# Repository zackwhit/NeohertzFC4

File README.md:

### About
NeohertzFC4 is my version of of a STM32F405 based flight controller, meant to operate quadcopters.
I developed this because I was curious what really went into the development of a flight controller; they seemed like relatively simple 
devices to cost so much. My goal was to develop something relatively simple and low-cost, and so that's why I opted to use the STM32F4 rather than an F7. Other 
open source designs (there aren't many!) aren't easy to interact with or order: they aren't in KiCAD and aren't on GitHub/Gitlab. So another one of my goals was to
provide a sort of template that would not only make my own development easier, but make it easier for other people as well. 

#### Features
- STM32F405RGTx main computing chip
- BMP280 barometer
- MMA8452QR1 accelerometer
- LIS3MDL magnometer
- AT7456 analog OSD chip
  
Bonus: LIS3DH accelerometer included as well, since I wanted to add support for it in betaflight. It doesn't have to be populated

### Updates
- July 19th, 2023: I ordered the parts for the first 5 prototypes after working on the design for about a week. All the parts should be here in about two weeks.

### Known Issues
- The JLCPCB information isn't exactly correct in REV001, I would not recomend ordering it at this stage unless you know what you're doing.

### Potential issues
- There aren't many (if any at all) alternative parts for certain ICs. If one were to go out of stock, a small redesign would have to be done to use a different solution.
- As of right now, the hardware is completely untested.

### How to build one!
- Order the PCBs through JLCPCB, I recomend only having them populate the passive components for you at this stage of the project.
- Order your components; I suggest through LCSC
- Assemble! This is a double sided PCB, but you can ignore the bottom side if you don't want to use the analog OSD chip included there.
- Profit.

### Future plans
As of the first revision, there is only one onboard BEC. This means there is only a 5V rail and no 9v (or 10v/12v) rails for a digital 
video system. I am planning on adding a second BEC for that purpose, but it didn't fit with my initial goal of having all the core components on
the top of the PCB. 

I'm also interested in creating a version of this with an AT32 chip instead of an STM32. As far as I can tell they are cheaper, but not necessarily more
available. I'm inclined to making a board that can have either an AT32 or an STM32 chip, that way you could just select whichever one is best at the time. 
Of course, this hinges on betaflight actually having decent support for AT32 chips, since I don't personally have time to add support. 

Other (optional) features I'm interested in adding:
- ELRS receiver built-in, both 900MHz and 2.4GHz options would be great so as to support long range flying.

#### License
GNU General Public License v3.0

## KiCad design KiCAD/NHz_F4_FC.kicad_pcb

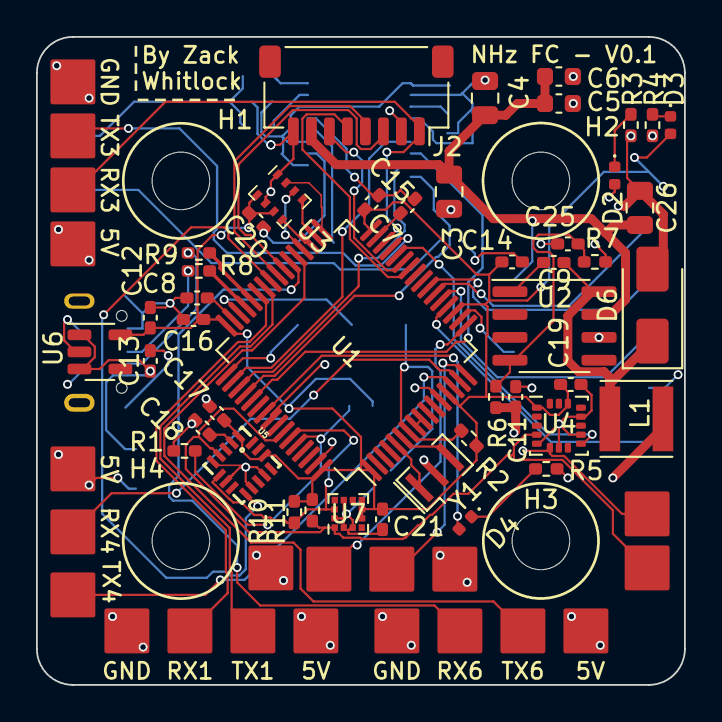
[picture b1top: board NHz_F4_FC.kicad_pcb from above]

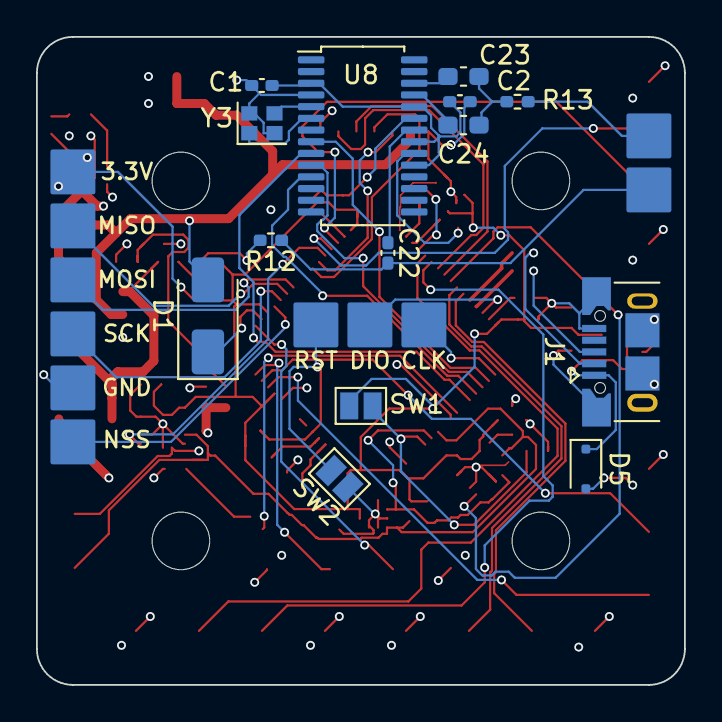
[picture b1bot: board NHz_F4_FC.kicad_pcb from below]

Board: 4 copper layers, 36.0 x 36.0 mm, 95 parts (25 on the bottom side), 66 nets.

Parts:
C1, C2, C9, C22: 100nF; C_0402_1005Metric_Pad0.74x0.62mm_HandSolder
C3, C4, C26: 4.7uF; C_0805_2012Metric
C5: 1uF; C_0603_1608Metric
C6: 0.1uF; C_0603_1608Metric
C7, C8: 2.2uF; C_0402_1005Metric_Pad0.74x0.62mm_HandSolder
C11, C12, C13, C14, C15, C16: 10uF; C_0402_1005Metric_Pad0.74x0.62mm_HandSolder
C17, C19, C20, C21: 4.7uF; C_0402_1005Metric_Pad0.74x0.62mm_HandSolder
C18: 0.1uF; C_0402_1005Metric_Pad0.74x0.62mm_HandSolder
C23, C24: 47uF; C_0603_1608Metric_Pad1.08x0.95mm_HandSolder
C25: 100p; C_0402_1005Metric_Pad0.74x0.62mm_HandSolder
D1: D_TVS; D_SMA
D2, D3, D4: LED; LED_0402_1005Metric
D5: D_Small; D_SOD-323F
D6: B340; D_SMA
H1, H2, H3, H4: MountingHole; MountingHole_3.2mm_M3
J1: USB_B_Micro; USB_Micro-B_XKB_U254-051T-4BH83-F1S
J2: Conn_01x08_Socket; JST_SH_SM08B-SRSS-TB_1x08-1MP_P1.00mm_Horizontal
L1: 22uH; L_Vishay_IFSC-1515AH_4x4x1.8mm
R1, R2, R6: 10k; R_0402_1005Metric_Pad0.72x0.64mm_HandSolder
R3, R4, R5: 1k; R_0402_1005Metric_Pad0.72x0.64mm_HandSolder
R7: 3.3k; R_0402_1005Metric_Pad0.72x0.64mm_HandSolder
R8, R9: 22; R_0402_1005Metric_Pad0.72x0.64mm_HandSolder
R10, R11: 2.2k; R_0402_1005Metric_Pad0.72x0.64mm_HandSolder
R12, R13: 75; R_0402_1005Metric_Pad0.72x0.64mm_HandSolder
SW1, SW2: SW_Push; SolderJumper-2_P1.3mm_Open_Pad1.0x1.5mm
TP1, TP2, TP3, TP4, TP5, TP6, TP7, TP8, TP9, TP10, TP11, TP12, TP13, TP14, TP15, TP16, TP17, TP18, TP19, TP20, TP21, TP22, TP23, TP24, TP25, TP26, TP27, TP28, TP29, TP30, TP31, TP32: TestPoint; SolderPad_2.5x2.5
U1: STM32F405RGTx; LQFP-64_10x10mm_P0.5mm
U2: TPS5420D; SOIC-8_3.9x4.9mm_P1.27mm
U3: BMP280; Bosch_LGA-8_2x2.5mm_P0.65mm_ClockwisePinNumbering
U4: LIS3DH; LGA-16_3x3mm_P0.5mm_LayoutBorder3x5y
U5: MMA8452QR1; QFN-16_0.5MM
U6: XC6219B332MR; SOT-23-5
U7: LIS3MDL; LGA-12_2x2mm_P0.5mm
U8: AT7456; TSSOP-28_4.4x9.7mm_P0.65mm
Y1: CSTCE8M00G52-R0; Resonator_SMD_Murata_CSTxExxV-3Pin_3.0x1.1mm
Y3: Crystal_GND24; Crystal_SMD_2016-4Pin_2.0x1.6mm

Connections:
+3.3V: C12.1, C14.1, C15.1, C16.1, C17.1, C19.1, C20.1, C21.1, D3.2 (A), R2.1, R10.2, R11.2, SW1.1, TP18.1, U1.1 (VBAT), U1.13 (VDDA), U1.19 (VDD), U1.32 (VDD), U1.48 (VDD), U1.64 (VDD), U3.6 (VDDIO), U3.8 (VDD), U4.1 (VDD_IO), U4.14 (VDD), U5.1 (VDDIO), U5.14 (VDD), U6.5 (VOUT), U7.5 (Vdd), U7.6 (Vdd_IO)
+5V: C11.1, C25.2, D2.2 (A), D5.2 (A), L1.2, R6.1, TP17.1, TP19.1, TP20.1, TP26.1, TP28.1
+BATT: C3.1, C4.1, C5.1, C6.1, C26.1, D1.2 (A2), J2.7, U2.7 (VIN)
/CUR: J2.2, U1.56 (PB4)
/LIS3DH_INT_PIN: U1.28 (PB2), U4.9 (INT2)
/M1: J2.6, U1.27 (PB1)
/M2: J2.5, U1.26 (PB0)
/M3: J2.4, U1.40 (PC9)
/M4: J2.3, U1.39 (PC8)
/MISO2: U1.35 (PB14), U3.5 (SDO)
/MISO3: U1.52 (PC11), U8.11 (SDOUT)
/MMA8451_INT_PIN: U1.41 (PA8), U5.9 (INT2)
/MOSI2: U1.36 (PB15), U3.3 (SDI)
/MOSI3: U1.53 (PC12), U8.9 (SDIN)
/RX3: J2.1, TP14.1, U1.30 (PB11)
/SCK2: U1.34 (PB13), U3.4 (SCK)
/SCK3: U1.51 (PC10), U8.10 (SCLK)
/SCL1: R11.1, TP11.1, U1.58 (PB6), U4.4 (SCL/SPC), U5.4 (SCL), U7.1 (SCL/SPC)
/SDA1: R10.1, TP12.1, U1.59 (PB7), U4.6 (SDA/SDI/SDO), U5.6 (SDA), U7.11 (SDA/SDI/SDO)
/SS2: U1.33 (PB12), U3.2 (CSB)
/SS3: U1.50 (PA15), U8.8 (CS)
/STM32F405RGTx/PA0_TX4: TP10.1, U1.14 (PA0)
/STM32F405RGTx/PA1_RX4: TP9.1, U1.15 (PA1)
/STM32F405RGTx/PA2_TX2: TP8.1, U1.16 (PA2)
/STM32F405RGTx/PA3_RX2: TP7.1, U1.17 (PA3)
/STM32F405RGTx/PA4_NSS1: TP6.1, U1.20 (PA4)
/STM32F405RGTx/PA5_SCK1: TP5.1, U1.21 (PA5)
/STM32F405RGTx/PA6_MISO1: TP4.1, U1.22 (PA6)
/STM32F405RGTx/PA7_MOSI1: TP3.1, U1.23 (PA7)
/STM32F405RGTx/PA9_TX1: TP2.1, U1.42 (PA9)
/STM32F405RGTx/PA10_RX1: TP1.1, U1.43 (PA10)
/STM32F405RGTx/PA13_SWDIO: TP30.1, U1.46 (PA13)
/STM32F405RGTx/PA14_SWCLK: TP29.1, U1.49 (PA14)
/STM32F405RGTx/PB10_TX3: TP13.1, U1.29 (PB10)
/STM32F405RGTx/PC0: U1.8 (PC0), U1.9 (PC1)
/STM32F405RGTx/PC6_TX6: TP16.1, U1.37 (PC6)
/STM32F405RGTx/PC7_RX6: TP15.1, U1.38 (PC7)
/STM32F405RGTx/RST: R2.2, SW2.2, TP25.1, U1.7 (NRST)
/Stat_LED: D4.2 (A), U1.55 (PB3)
/USB+: R8.2, U1.45 (PA12)
/USB-: R9.1, U1.44 (PA11)
/V_IN: C22.2, R12.1, TP31.1
/V_OUT: R13.2, TP32.1
GND: C1.2, C2.2, C3.2, C4.2, C5.2, C6.2, C7.1, C8.1, C11.2, C12.2, C13.2, C14.2, C15.2, C16.2, C17.2, C18.1, C19.2, C20.2, C21.2, C26.2, D1.1 (A1), D6.2 (A), J1.5 (GND), J1.6 (Shield), J2.8, R1.2, R3.2, R4.2, R5.2, R7.2, R12.2, SW2.1, TP21.1, TP22.1, TP23.1, TP24.1, TP27.1, U1.12 (VSSA), U1.18 (VSS), U1.63 (VSS), U2.6 (GND), U3.1 (GND), U3.7 (GND), U4.5 (GND), U4.7 (SDO/SA0), U4.10 (GND), U4.12 (GND), U5.5 (GND), U5.7 (SA0), U5.10 (GND), U5.12 (GND), U6.2 (GND), U7.2 (GND), U7.3 (GND), U7.9 (SDO/SA1), U7.12 (GND), U8.4 (DGND), U8.20 (AVGND), U8.23 (PGND), Y1.2, Y3.2, Y3.4
unnamed: C23.2, C24.2, R13.1
unnamed: D2.1 (K), R3.1
unnamed: D3.1 (K), R4.1
unnamed: D4.1 (K), R5.1
unnamed: C9.1, D6.1 (K), L1.1, U2.8 (PH)
unnamed: J1.3 (D+), R8.1
unnamed: J1.2 (D-), R9.2
unnamed: R1.1, SW1.2, U1.60 (BOOT0)
unnamed: U1.5 (PH0), Y1.1
unnamed: U1.6 (PH1), Y1.3
unnamed: C7.2, U1.31 (VCAP_1)
unnamed: C8.2, U1.47 (VCAP_2)
unnamed: C9.2, U2.1 (BOOT)
unnamed: C25.1, R6.2, R7.1, U2.4 (VSNS)
unnamed: C18.2, U5.2 (BYP)
unnamed: C1.1, C2.1, U8.3 (DVDD), U8.19 (RESET), U8.21 (AVDD), U8.24 (PVDD)
unnamed: U8.5 (CLKIN), Y3.3
unnamed: C24.1, U8.25 (SAG)
unnamed: C22.1, U8.22 (VIN)
unnamed: C23.1, U8.26 (VOUT)
unnamed: U8.6 (XFB), Y3.1
VBUS: C13.1, D5.1 (K), J1.1 (VBUS), U6.1 (VIN), U6.3 (CE)

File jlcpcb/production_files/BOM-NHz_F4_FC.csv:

Comment,Designator,Footprint,LCSC
75,"R12,R13",R_0402_1005Metric_Pad0.72x0.64mm_HandSolder,C114757
10k,"R1,R2,R6",R_0402_1005Metric_Pad0.72x0.64mm_HandSolder,C11616
2.2uF,"C7,C8",C_0402_1005Metric_Pad0.74x0.62mm_HandSolder,C12530
47uF,"C23,C24",C_0603_1608Metric_Pad1.08x0.95mm_HandSolder,C140782
100nF,"C1,C18,C2,C22,C6,C9",C_0402_1005Metric_Pad0.74x0.62mm_HandSolder,C1525
1k,"R3,R4,R5",R_0402_1005Metric_Pad0.72x0.64mm_HandSolder,C1527
10uF,"C11,C12,C13,C14,C15,C16",C_0402_1005Metric_Pad0.74x0.62mm_HandSolder,C15525
1uF,C5,C_0603_1608Metric,C15849
2.2k,"R10,R11",R_0402_1005Metric_Pad0.72x0.64mm_HandSolder,C25879
3.3k,R7,R_0402_1005Metric_Pad0.72x0.64mm_HandSolder,C25890
100p,"C25,D6",C_0402_1005Metric_Pad0.74x0.62mm_HandSolder,C3018525
22,"R8,R9",R_0402_1005Metric_Pad0.72x0.64mm_HandSolder,C325383
LED,D3,LED_0402_1005Metric,C434447
LED,D2,LED_0402_1005Metric,C434448
4.7uF,"C26,C3,C4",C_0805_2012Metric,C76651
LED,D4,LED_0402_1005Metric,C965790
4.7uF,"C17,C19,C20,C21",C_0402_1005Metric_Pad0.74x0.62mm_HandSolder,C98192
XC6219B332MR,U6,SOT-23-5,
LIS3DH,U4,LGA-16_3x3mm_P0.5mm_LayoutBorder3x5y,
TestPoint,TP2,SolderPad_2.5x2.5,
22uH,L1,L_Vishay_IFSC-1515AH_4x4x1.8mm,
MountingHole,H2,MountingHole_3.2mm_M3,
TestPoint,TP24,SolderPad_2.5x2.5,
TestPoint,TP20,SolderPad_2.5x2.5,
TestPoint,TP17,SolderPad_2.5x2.5,
TestPoint,TP23,SolderPad_2.5x2.5,
MountingHole,H4,MountingHole_3.2mm_M3,
TestPoint,TP28,SolderPad_2.5x2.5,
BMP280,U3,Bosch_LGA-8_2x2.5mm_P0.65mm_ClockwisePinNumbering,
MountingHole,H1,MountingHole_3.2mm_M3,
TestPoint,TP27,SolderPad_2.5x2.5,
TestPoint,TP26,SolderPad_2.5x2.5,
TestPoint,TP10,SolderPad_2.5x2.5,
TestPoint,TP13,SolderPad_2.5x2.5,
MountingHole,H3,MountingHole_3.2mm_M3,
TestPoint,TP14,SolderPad_2.5x2.5,
TestPoint,TP11,SolderPad_2.5x2.5,
 	CSTCE8M00G52-R0,Y1,Resonator_SMD_Murata_CSTxExxV-3Pin_3.0x1.1mm,
TestPoint,TP16,SolderPad_2.5x2.5,
TestPoint,TP1,SolderPad_2.5x2.5,
TestPoint,TP21,SolderPad_2.5x2.5,
Conn_01x08_Socket,J2,JST_SH_SM08B-SRSS-TB_1x08-1MP_P1.00mm_Horizontal,
TestPoint,TP8,SolderPad_2.5x2.5,
TPS5420D,U2,SOIC-8_3.9x4.9mm_P1.27mm,
STM32F405RGTx,U1,LQFP-64_10x10mm_P0.5mm,
TestPoint,TP15,SolderPad_2.5x2.5,
TestPoint,TP9,SolderPad_2.5x2.5,
TestPoint,TP19,SolderPad_2.5x2.5,
MMA8452QR1,U5,QFN-16_0.5MM,
TestPoint,TP7,SolderPad_2.5x2.5,
TestPoint,TP12,SolderPad_2.5x2.5,
LIS3MDL,U7,LGA-12_2x2mm_P0.5mm,
TestPoint,TP30,SolderPad_2.5x2.5,
TestPoint,TP5,SolderPad_2.5x2.5,
USB_B_Micro,J1,USB_Micro-B_XKB_U254-051T-4BH83-F1S,
D_Small,D5,D_SOD-323F,
TestPoint,TP4,SolderPad_2.5x2.5,
TestPoint,TP6,SolderPad_2.5x2.5,
TestPoint,TP3,SolderPad_2.5x2.5,
TestPoint,TP25,SolderPad_2.5x2.5,
D_TVS,D1,D_SMA,
TestPoint,TP32,SolderPad_2.5x2.5,
TestPoint,TP29,SolderPad_2.5x2.5,
TestPoint,TP18,SolderPad_2.5x2.5,
Crystal_GND24,Y3,Crystal_SMD_2016-4Pin_2.0x1.6mm,
TestPoint,TP31,SolderPad_2.5x2.5,
TestPoint,TP22,SolderPad_2.5x2.5,
AT7456,U8,TSSOP-28_4.4x9.7mm_P0.65mm,
SW_Push,SW2,SolderJumper-2_P1.3mm_Open_Pad1.0x1.5mm,
SW_Push,SW1,SolderJumper-2_P1.3mm_Open_Pad1.0x1.5mm,

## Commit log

2023-07-19 Create COPYING
2023-07-22 Added kicad files
2023-07-22 Added screenshot
